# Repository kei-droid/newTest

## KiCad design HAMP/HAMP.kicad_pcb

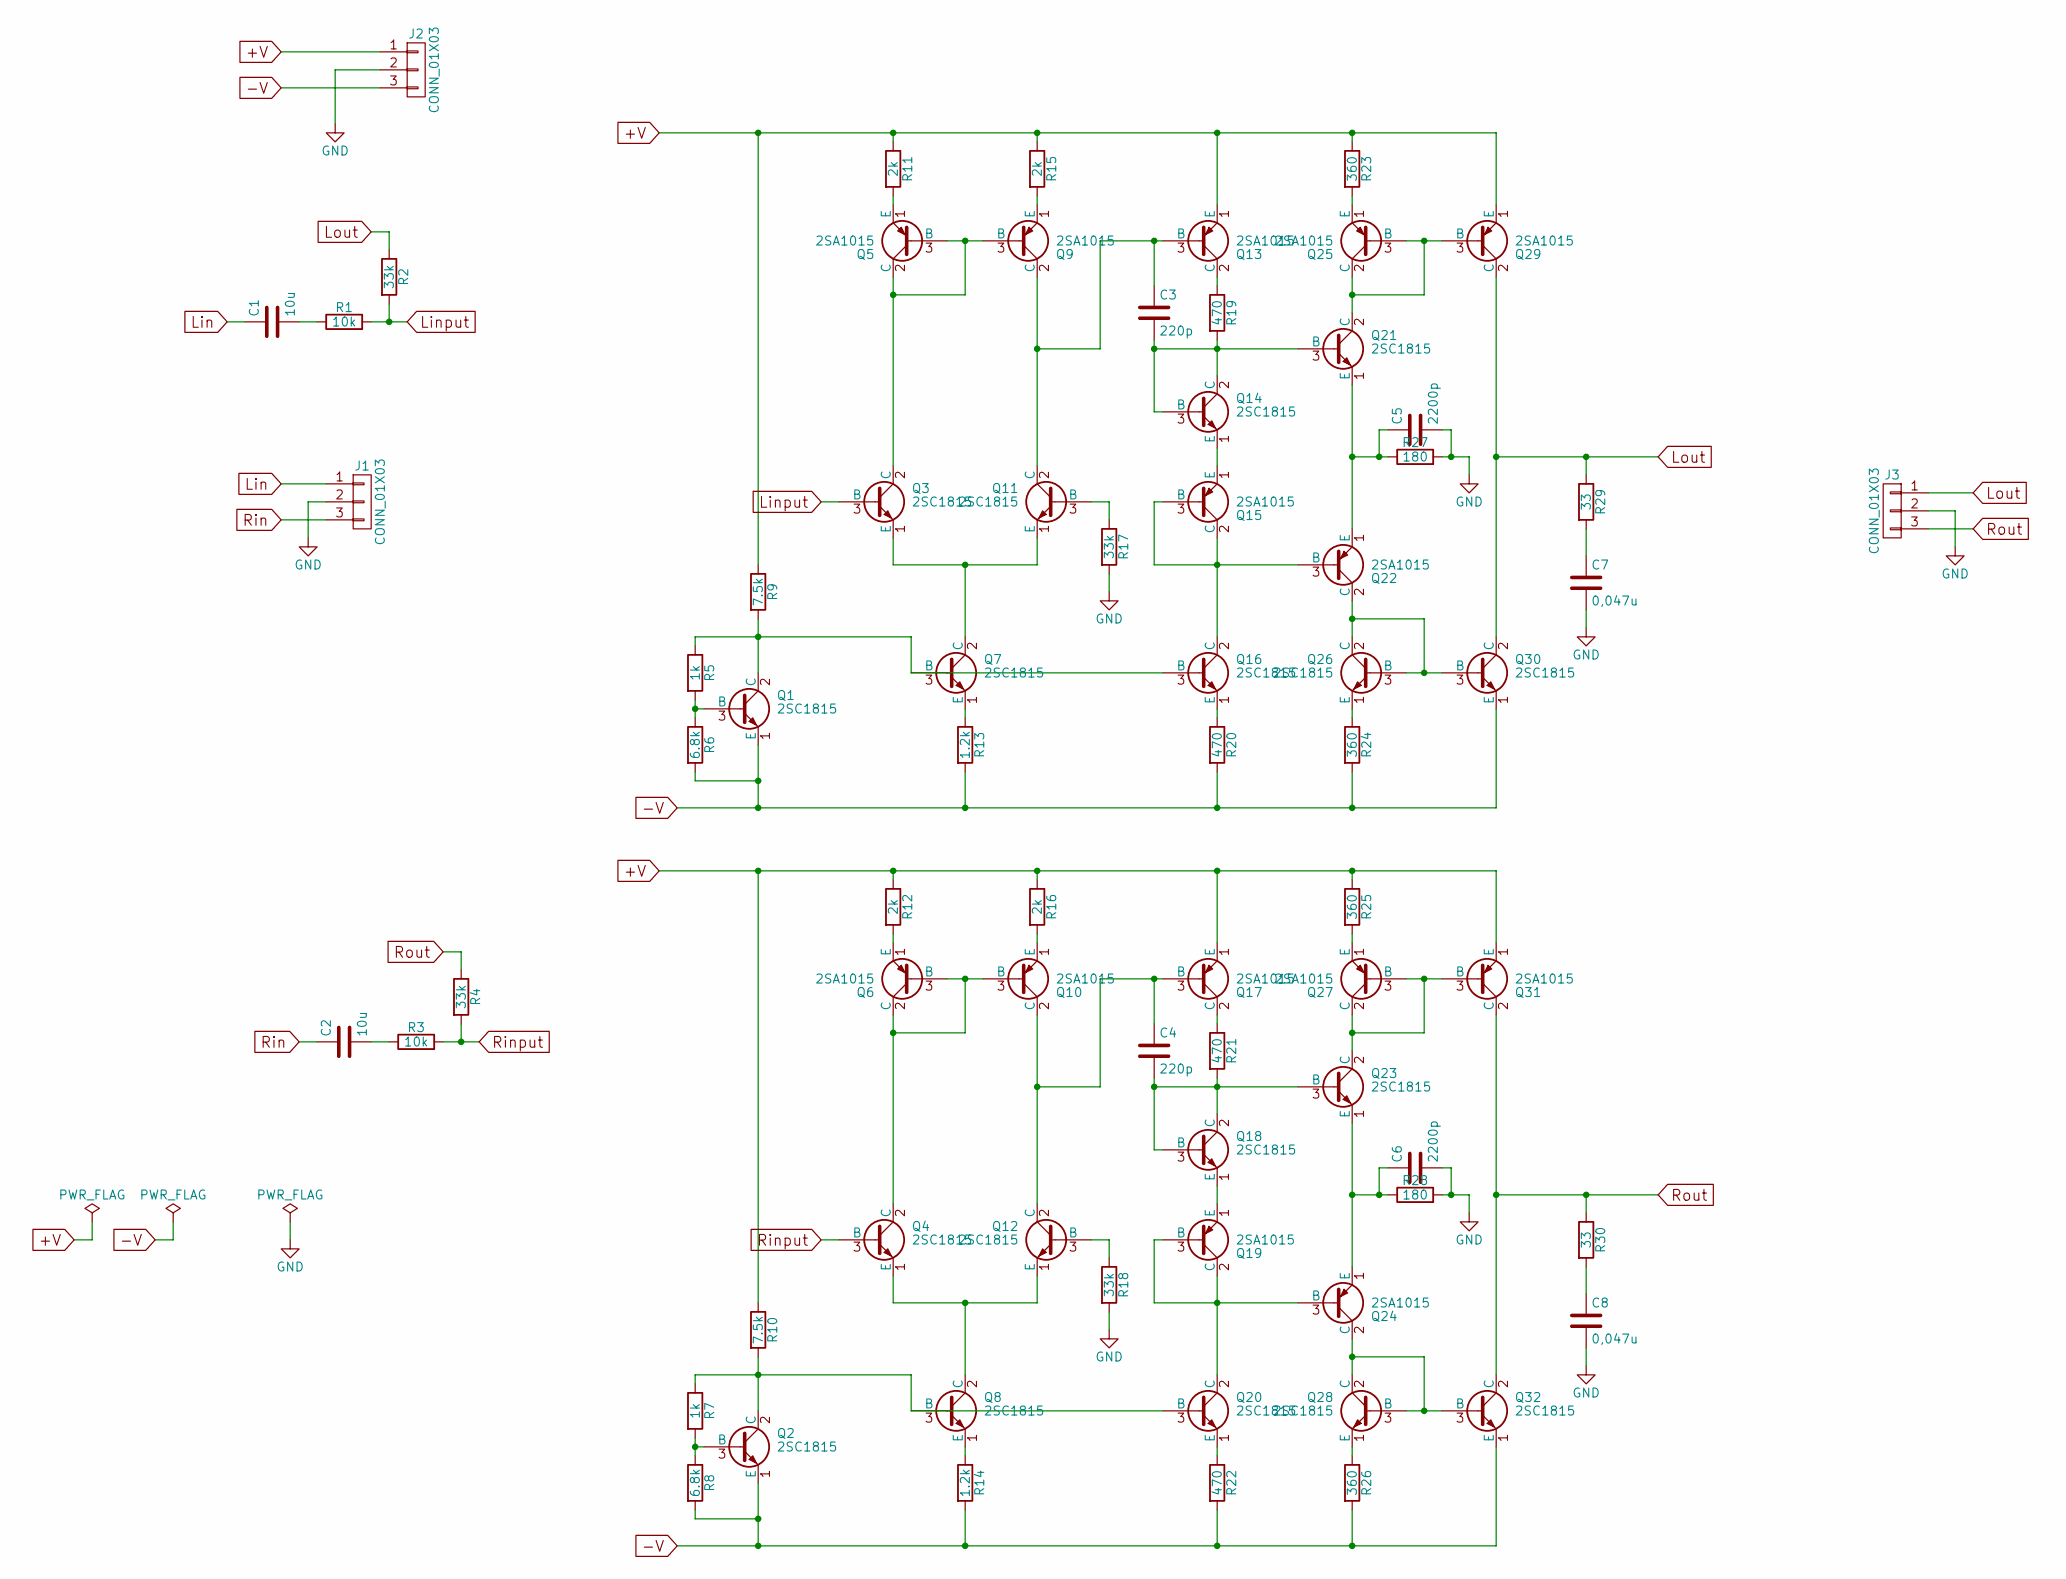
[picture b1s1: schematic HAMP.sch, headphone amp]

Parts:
C1, C2: 10u; C_Disc_D3.0mm_W1.6mm_P2.50mm
C3, C4: 220p; C_Disc_D3.0mm_W1.6mm_P2.50mm
C5, C6: 2200p; C_Disc_D3.0mm_W1.6mm_P2.50mm
C7, C8: 0,047u; C_Disc_D3.0mm_W1.6mm_P2.50mm
J1, J2, J3: CONN_01X03; PINHEAD1-3
Q1, Q2, Q3, Q4, Q7, Q8, Q11, Q12, Q14, Q16, Q18, Q20, Q21, Q23, Q26, Q28, Q30, Q32: 2SC1815; TO-92_Molded_Narrow
Q5, Q6, Q9, Q10, Q13, Q15, Q17, Q19, Q22, Q24, Q25, Q27, Q29, Q31: 2SA1015; TO-92_Molded_Narrow
R1, R3: 10k; R_Axial_DIN0207_L6.3mm_D2.5mm_P10.16mm_Horizontal
R2, R4, R17, R18: 33k; R_Axial_DIN0207_L6.3mm_D2.5mm_P10.16mm_Horizontal
R5, R7: 1k; R_Axial_DIN0207_L6.3mm_D2.5mm_P10.16mm_Horizontal
R6, R8: 6.8k; R_Axial_DIN0207_L6.3mm_D2.5mm_P10.16mm_Horizontal
R9, R10: 7.5k; R_Axial_DIN0207_L6.3mm_D2.5mm_P10.16mm_Horizontal
R11, R12, R15, R16: 2k; R_Axial_DIN0207_L6.3mm_D2.5mm_P10.16mm_Horizontal
R13, R14: 1.2k; R_Axial_DIN0207_L6.3mm_D2.5mm_P10.16mm_Horizontal
R19, R20, R21, R22: 470; R_Axial_DIN0207_L6.3mm_D2.5mm_P10.16mm_Horizontal
R23, R24, R25, R26: 360; R_Axial_DIN0207_L6.3mm_D2.5mm_P10.16mm_Horizontal
R27, R28: 180; R_Axial_DIN0207_L6.3mm_D2.5mm_P10.16mm_Horizontal
R29, R30: 33; R_Axial_DIN0207_L6.3mm_D2.5mm_P10.16mm_Horizontal

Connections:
+V: J2.1, Q13.1 (E), Q17.1 (E), Q29.1 (E), Q31.1 (E), R9.1, R10.1, R11.1, R12.1, R15.1, R16.1, R23.1, R25.1
-V: J2.3, Q1.1 (E), Q2.1 (E), Q30.1 (E), Q32.1 (E), R6.2, R8.2, R13.2, R14.2, R20.2, R22.2, R24.2, R26.2
GND: C5.2, C6.2, C7.2, C8.2, J1.2, J2.2, J3.2, R17.2, R18.2, R27.2, R28.2
Lin: C1.1, J1.1
Linput: Q3.3 (B), R1.2, R2.2
Lout: J3.1, Q29.2 (C), Q30.2 (C), R2.1, R29.1
unnamed: C1.2, R1.1
unnamed: C2.2, R3.1
unnamed: C3.1, Q9.2 (C), Q11.2 (C), Q13.3 (B)
unnamed: C3.2, Q14.2 (C), Q14.3 (B), Q21.3 (B), R19.2
unnamed: C4.1, Q10.2 (C), Q12.2 (C), Q17.3 (B)
unnamed: C4.2, Q18.2 (C), Q18.3 (B), Q23.3 (B), R21.2
unnamed: C5.1, Q21.1 (E), Q22.1 (E), R27.1
unnamed: C6.1, Q23.1 (E), Q24.1 (E), R28.1
unnamed: C7.1, R29.2
unnamed: C8.1, R30.2
unnamed: Q1.2 (C), Q7.3 (B), Q16.3 (B), R5.1, R9.2
unnamed: Q1.3 (B), R5.2, R6.1
unnamed: Q2.2 (C), Q8.3 (B), Q20.3 (B), R7.1, R10.2
unnamed: Q2.3 (B), R7.2, R8.1
unnamed: Q3.2 (C), Q5.2 (C), Q5.3 (B), Q9.3 (B)
unnamed: Q5.1 (E), R11.2
unnamed: Q6.1 (E), R12.2
unnamed: Q7.1 (E), R13.1
unnamed: Q8.1 (E), R14.1
unnamed: Q9.1 (E), R15.2
unnamed: Q10.1 (E), R16.2
unnamed: Q4.2 (C), Q6.2 (C), Q6.3 (B), Q10.3 (B)
unnamed: Q3.1 (E), Q7.2 (C), Q11.1 (E)
unnamed: Q11.3 (B), R17.1
unnamed: Q4.1 (E), Q8.2 (C), Q12.1 (E)
unnamed: Q12.3 (B), R18.1
unnamed: Q13.2 (C), R19.1
unnamed: Q14.1 (E), Q15.1 (E)
unnamed: Q15.2 (C), Q15.3 (B), Q16.2 (C), Q22.3 (B)
unnamed: Q16.1 (E), R20.1
unnamed: Q17.2 (C), R21.1
unnamed: Q18.1 (E), Q19.1 (E)
unnamed: Q19.2 (C), Q19.3 (B), Q20.2 (C), Q24.3 (B)
unnamed: Q20.1 (E), R22.1
unnamed: Q21.2 (C), Q25.2 (C), Q25.3 (B), Q29.3 (B)
unnamed: Q22.2 (C), Q26.2 (C), Q26.3 (B), Q30.3 (B)
unnamed: Q23.2 (C), Q27.2 (C), Q27.3 (B), Q31.3 (B)
unnamed: Q24.2 (C), Q28.2 (C), Q28.3 (B), Q32.3 (B)
unnamed: Q25.1 (E), R23.2
unnamed: Q26.1 (E), R24.1
unnamed: Q27.1 (E), R25.2
unnamed: Q28.1 (E), R26.1
Rin: C2.1, J1.3
Rinput: Q4.3 (B), R3.2, R4.2
Rout: J3.3, Q31.2 (C), Q32.2 (C), R4.1, R30.1

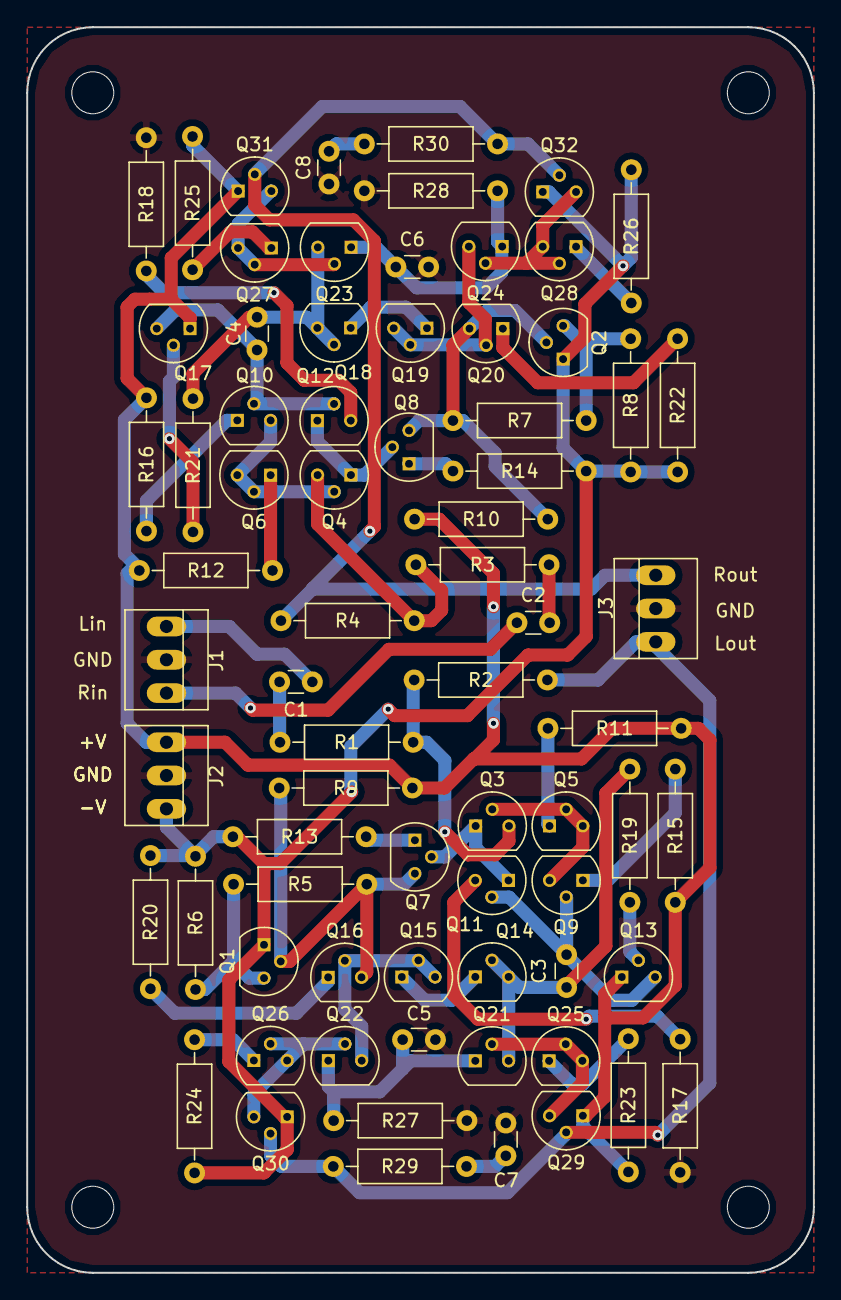
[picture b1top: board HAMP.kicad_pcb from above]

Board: 2 copper layers, 60.0 x 95.0 mm, 73 parts (0 on the bottom side), 51 nets.

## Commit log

2020-04-14 1st commit
2020-04-14 2nd commit
